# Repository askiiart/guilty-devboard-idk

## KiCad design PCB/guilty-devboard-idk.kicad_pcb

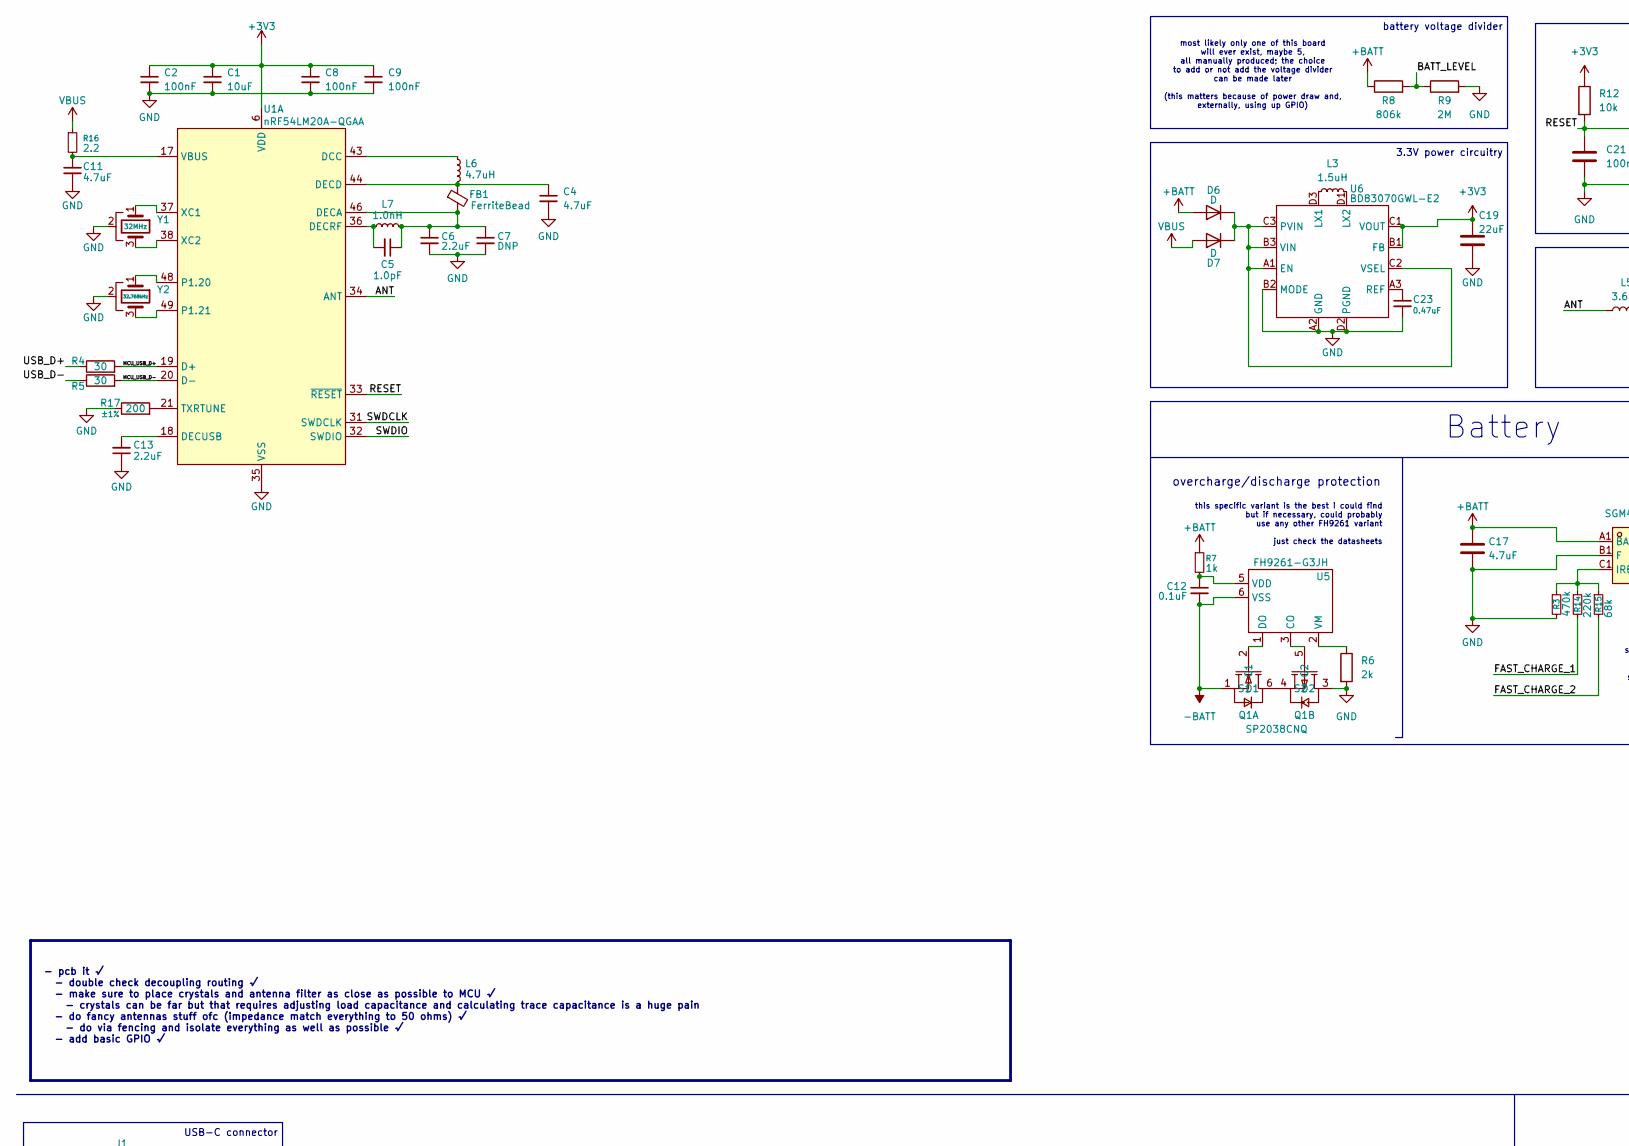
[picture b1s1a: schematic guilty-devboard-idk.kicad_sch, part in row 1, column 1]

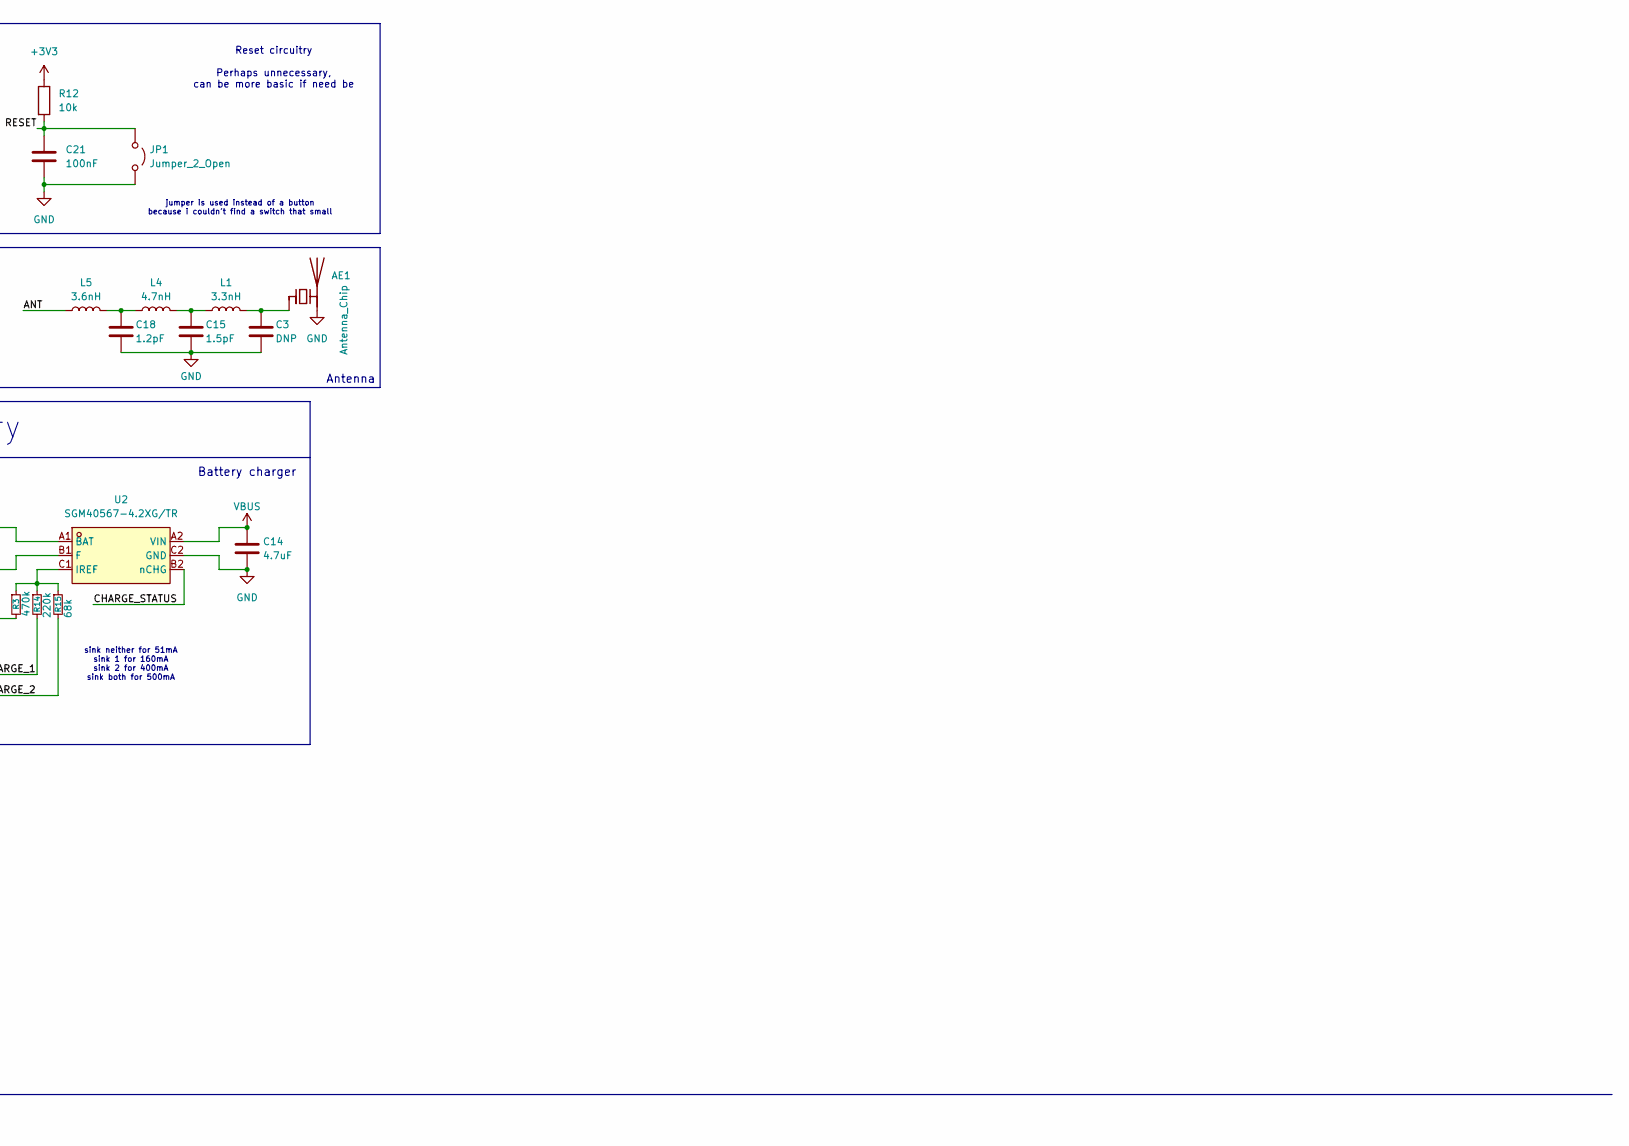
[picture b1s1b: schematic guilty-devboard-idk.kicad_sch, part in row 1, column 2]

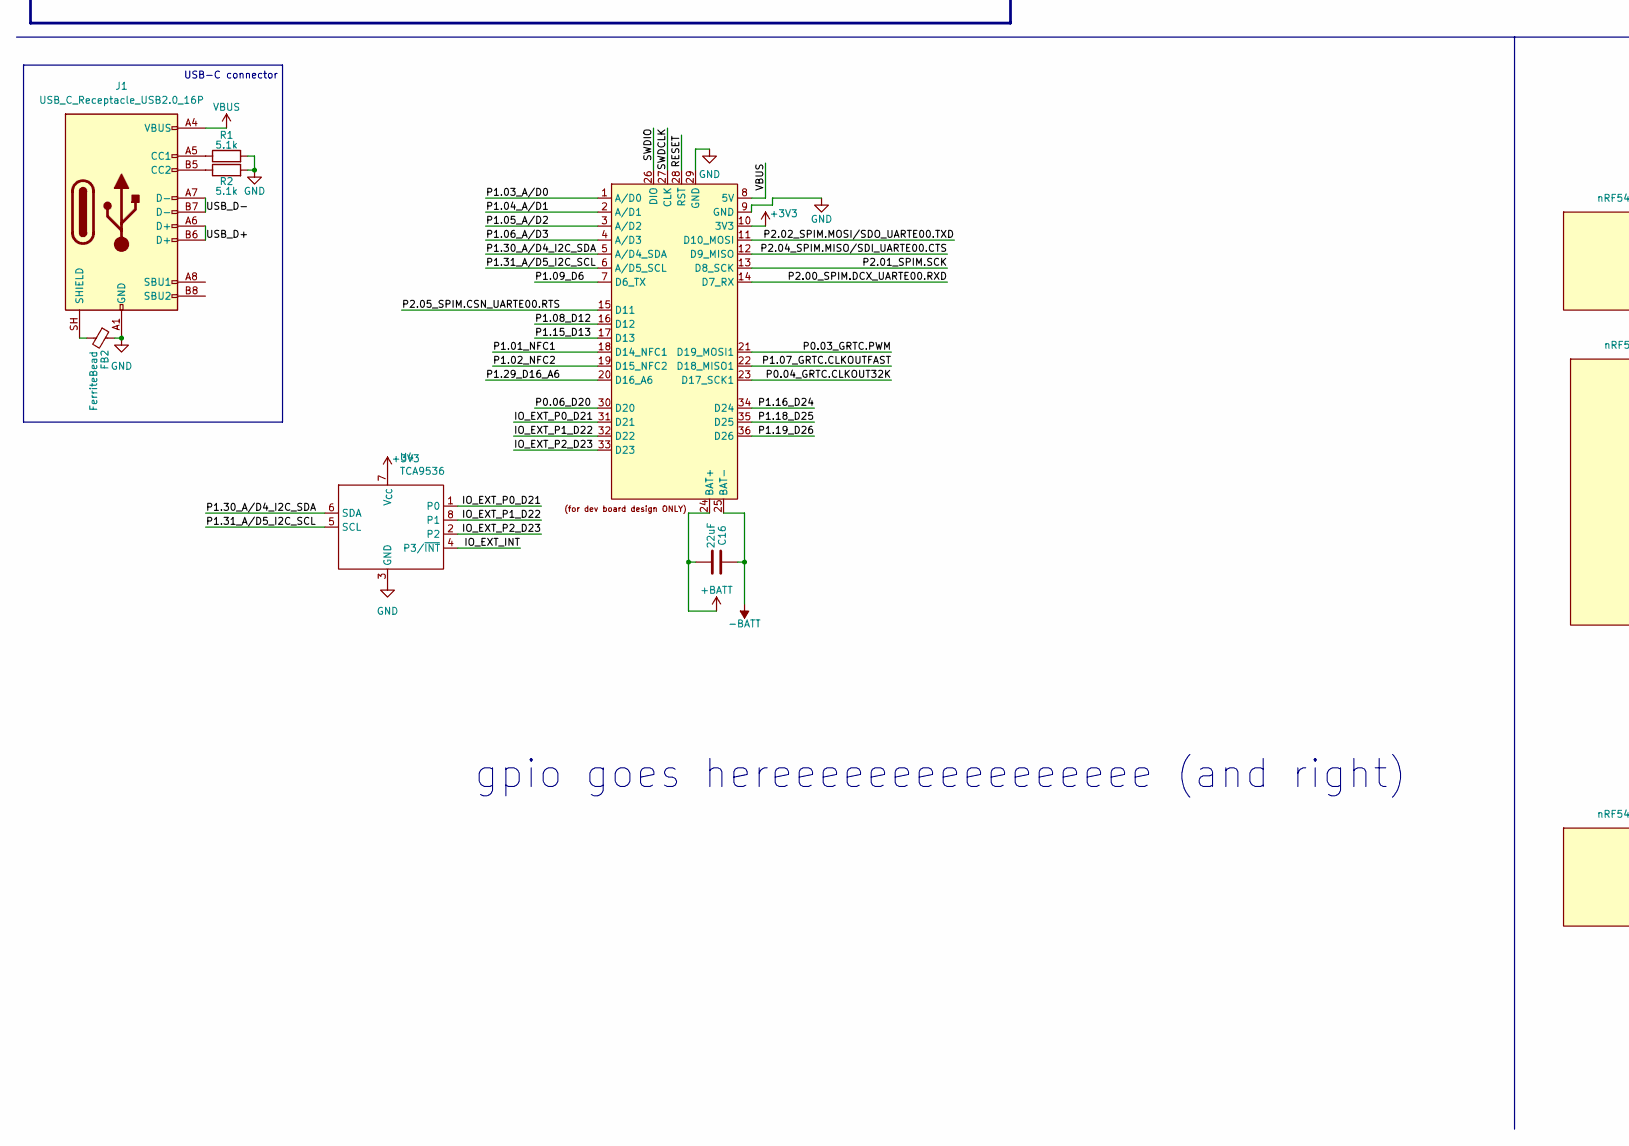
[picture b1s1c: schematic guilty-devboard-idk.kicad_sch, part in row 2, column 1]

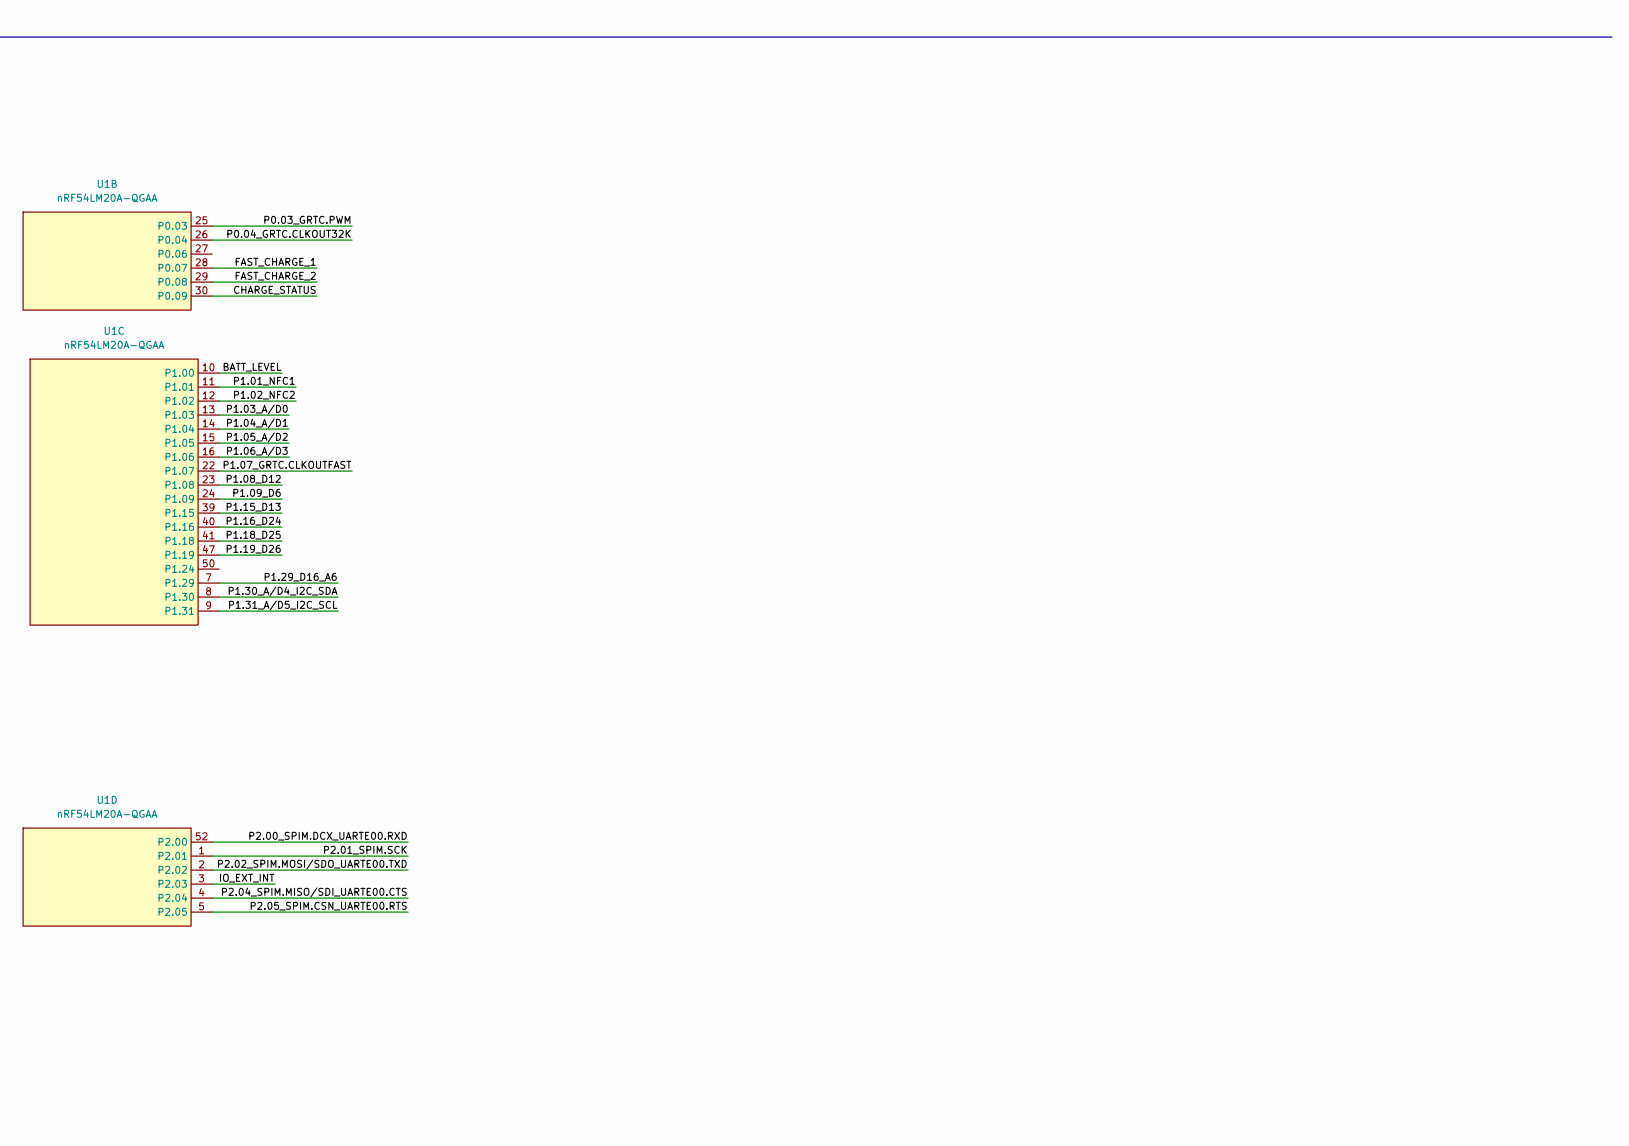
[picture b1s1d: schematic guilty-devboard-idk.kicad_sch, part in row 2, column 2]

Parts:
AE1: Antenna_Chip; 2450AT18D0100001E_L
C1: 10uF; C_0402_1005Metric
C2, C8, C9, C21: 100nF; C_0201_0603Metric
C3, C7: DNP; C_0201_0603Metric
C4, C11, C14, C17: 4.7uF; C_0201_0603Metric
C5: 1.0pF; C_0201_0603Metric
C6, C13: 2.2uF; C_0201_0603Metric
C12: 0.1uF; C_0201_0603Metric
C15: 1.5pF; C_0201_0603Metric
C16, C19: 22uF; C_0402_1005Metric
C18: 1.2pF; C_0201_0603Metric
C23: 0.47uF; C_0201_0603Metric
D6, D7: D; D_SOD-882
FB1, FB2: FerriteBead; L_0201_0603Metric
J1: USB_C_Receptacle_USB2.0_16P; USB_C_Receptacle_Amphenol_124019772112A
JP1: Jumper_2_Open; R_0603_1608Metric
L1: 3.3nH; L_0201_0603Metric
L3: 1.5uH; L_0603_1608Metric
L4: 4.7nH; L_0201_0603Metric
L5: 3.6nH; L_0201_0603Metric
L6: 4.7uH; L_0402_1005Metric
L7: 1.0nH; L_0201_0603Metric
Q1: SP2038CNQ; PDFN-6_L2.0-W2.0-P0.65-BL-EP-1; LCSC Part C41355091
R1, R2: 5.1k; R_0201_0603Metric
R3: 470k; R_0201_0603Metric
R4, R5: 30; R_0201_0603Metric
R6: 2k; R_0201_0603Metric
R7: 1k; R_0201_0603Metric
R8: 806k; R_0201_0603Metric
R9: 2M; R_0201_0603Metric
R12: 10k; R_0201_0603Metric
R14: 220k; R_0201_0603Metric
R15: 68k; R_0201_0603Metric
R16: 2.2; R_0201_0603Metric
R17: 200; R_0201_0603Metric; Tolerance ±1%
U1: nRF54LM20A-QGAA; QFN-52-1EP_6x6mm_P0.4mm_EP4.7x4.7mm_ThermalVias
U2: SGM40567-4.2XG/TR; WLCSP-6_L1.2-W0.9-R3-C2-P0.40-TL; LCSC Part C5141336
U3: Guilty Devboard Xrd pads
U4: TCA9536
U5: FH9261-G3JH; SOT-23-6
U6: BD83070GWL-E2; BD83070GWL
Y1: 32MHz; Crystal_SMD_1210-4Pin_1.2x1.0mm
Y2: 32.768kHz; Crystal_SMD_1210-4Pin_1.2x1.0mm

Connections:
+3V3: C1.1, C2.1, C8.1, C9.1, C19.1, R12.1, U1.6 (VDD), U1.42 (VDD), U1.51 (VDD), U3.10 (3V3), U4.7 (V_{CC}), U6.B1 (FB), U6.C1 (VOUT)
+BATT: C16.2, C17.1, D6.2 (A), R7.1, R8.1, U2.A1 (BAT), U3.24 (BAT+)
-BATT: C12.2, C16.1, Q1.1 (S1), U3.25 (BAT-), U5.6 (VSS)
/ANT: L5.1, U1.34 (ANT)
/BATT_LEVEL: R8.2, R9.1, U1.10 (P1.00)
/CHARGE_STATUS: U1.30 (P0.09), U2.B2 (nCHG)
/FAST_CHARGE_1: R14.2, U1.28 (P0.07)
/FAST_CHARGE_2: R15.2, U1.29 (P0.08)
/IO_EXT_INT: U1.3 (P2.03), U4.4 (P3/~INT)
/IO_EXT_P0_D21: U3.31 (D21), U4.1 (P0)
/IO_EXT_P1_D22: U3.32 (D22), U4.8 (P1)
/IO_EXT_P2_D23: U3.33 (D23), U4.2
/MCU_USB_D+: R4.2, U1.19 (D+)
/MCU_USB_D-: R5.2, U1.20 (D-)
/P0.03_GRTC.PWM: U1.25 (P0.03), U3.21 (D19_MOSI1)
/P0.04_GRTC.CLKOUT32K: U1.26 (P0.04), U3.23 (D17_SCK1)
/P0.06_D20: U3.30 (D20)
/P1.01_NFC1: U1.11 (P1.01), U3.18 (D14_NFC1)
/P1.02_NFC2: U1.12 (P1.02), U3.19 (D15_NFC2)
/P1.03_A/D0: U1.13 (P1.03), U3.1 (A/D0)
/P1.04_A/D1: U1.14 (P1.04), U3.2 (A/D1)
/P1.05_A/D2: U1.15 (P1.05), U3.3 (A/D2)
/P1.06_A/D3: U1.16 (P1.06), U3.4 (A/D3)
/P1.07_GRTC.CLKOUTFAST: U1.22 (P1.07), U3.22 (D18_MISO1)
/P1.08_D12: U1.23 (P1.08), U3.16 (D12)
/P1.09_D6: U1.24 (P1.09), U3.7 (D6_TX)
/P1.15_D13: U1.39 (P1.15), U3.17 (D13)
/P1.16_D24: U1.40 (P1.16), U3.34 (D24)
/P1.18_D25: U1.41 (P1.18), U3.35 (D25)
/P1.19_D26: U1.47 (P1.19), U3.36 (D26)
/P1.29_D16_A6: U1.7 (P1.29), U3.20 (D16_A6)
/P1.30_A/D4_I2C_SDA: U1.8 (P1.30), U3.5 (A/D4_SDA), U4.6 (SDA)
/P1.31_A/D5_I2C_SCL: U1.9 (P1.31), U3.6 (A/D5_SCL), U4.5 (SCL)
/P2.00_SPIM.DCX_UARTE00.RXD: U1.52 (P2.00), U3.14 (D7_RX)
/P2.01_SPIM.SCK: U1.1 (P2.01), U3.13 (D8_SCK)
/P2.02_SPIM.MOSI/SDO_UARTE00.TXD: U1.2 (P2.02), U3.11 (D10_MOSI)
/P2.04_SPIM.MISO/SDI_UARTE00.CTS: U1.4 (P2.04), U3.12 (D9_MISO)
/P2.05_SPIM.CSN_UARTE00.RTS: U1.5 (P2.05), U3.15 (D11)
/RESET: C21.1, JP1.1 (A), R12.2, U1.33 (~RESET), U3.28 (RST)
/SWDCLK: U1.31 (SWDCLK), U3.27 (CLK)
/SWDIO: U1.32 (SWDIO), U3.26 (DIO)
/USB_D+: J1.A6 (D+), J1.B6 (D+), R4.1
/USB_D-: J1.A7 (D-), J1.B7 (D-), R5.1
GND: AE1.2 (PCB_Trace), C1.2, C2.2, C3.1, C4.2, C6.2, C7.2, C8.2, C9.2, C11.2, C13.1, C14.2, C15.1, C17.2, C18.1, C19.2, C21.2, C23.2, FB2.1, J1.A1 (GND), J1.A12 (GND), J1.B1 (GND), J1.B12 (GND), JP1.2 (B), Q1.3 (D2), R1.2, R2.2, R3.2, R6.2, R9.2, R17.1, U1.35 (VSS), U1.45 (VSS), U1.53 (VSS), U2.B1 (F), U2.C2 (GND), U3.9 (GND), U3.29 (GND), U4.3 (GND), U6.A2 (GND), U6.B2 (MODE), U6.D2 (PGND), Y1.2, Y2.2
unnamed: AE1.1 (FEED), C3.2, L1.2
unnamed: C15.2, L1.1, L4.2
unnamed: C18.2, L4.1, L5.2
unnamed: D6.1 (K), D7.1 (K), U6.A1 (EN), U6.B3 (VIN), U6.C2 (VSEL), U6.C3 (PVIN)
unnamed: J1.A5 (CC1), R1.1
unnamed: J1.B5 (CC2), R2.1
unnamed: FB2.2, J1.SH (SHIELD)
unnamed: Q1.4 (S2), Q1.6 (D1)
unnamed: Q1.2 (G1), U5.1 (DO)
unnamed: Q1.5 (G2), U5.3 (CO)
unnamed: L6.1, U1.43 (DCC)
unnamed: C5.1, C6.1, C7.1, FB1.2, L7.2, U1.46 (DECA)
unnamed: C4.1, FB1.1, L6.2, U1.44 (DECD)
unnamed: C5.2, L7.1, U1.36 (DECRF)
unnamed: C13.2, U1.18 (DECUSB)
unnamed: U1.48 (P1.20), Y2.1
unnamed: U1.49 (P1.21), Y2.3
unnamed: R17.2, U1.21 (TXRTUNE)
unnamed: C11.1, R16.2, U1.17 (VBUS)
unnamed: U1.37 (XC1), Y1.1
unnamed: U1.38 (XC2), Y1.3
unnamed: R3.1, R14.1, R15.1, U2.C1 (IREF)
unnamed: C12.1, R7.2, U5.5 (VDD)
unnamed: R6.1, U5.2 (VM)
unnamed: L3.1, U6.D3 (LX1)
unnamed: L3.2, U6.D1 (LX2)
unnamed: C23.1, U6.A3 (REF)
VBUS: C14.1, D7.2 (A), J1.A4 (VBUS), J1.A9 (VBUS), J1.B4 (VBUS), J1.B9 (VBUS), R16.1, U2.A2 (VIN), U3.8 (5V)

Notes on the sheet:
Reset circuitry Perhaps unnecessary, can be more basic if need be
Battery charger
battery voltage divider
- pcb it √ - double check decoupling routing √ - make sure to place crystals and antenna filter as close as possible to MCU √ - crystals can be far but that requires adjusting load capacitance and calculating trace capacitance is a huge pain - do fancy antennas stuff ofc (impedance match everything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
jumper is used instead of a button because i couldn't find a switch that small
this specific variant is the best i could find but if necessary, could probably use any other FH9261 variant just check the datasheets
Antenna
USB-C connector
gpio goes hereeeeeeeeeeeeeeee (and right)
Battery
overcharge/discharge protection
3.3V power circuitry
sink neither for 51mA sink 1 for 160mA sink 2 for 400mA sink both for 500mA
most likely only one of this board will ever exist, maybe 5, all manually produced; the choice to add or not add the voltage divider can be made later (this matters because of power draw and, externally, using up GPIO)

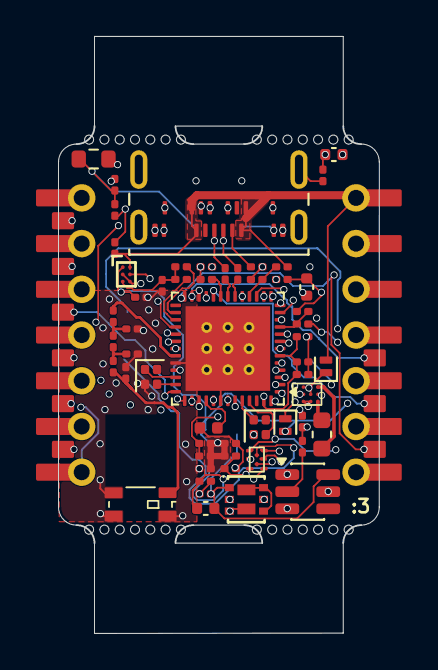
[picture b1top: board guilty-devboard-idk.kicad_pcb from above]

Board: 6 copper layers, 17.8 x 33.2 mm, 56 parts (0 on the bottom side), 71 nets.

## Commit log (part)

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2026-01-15 initial version - pretty much finished schematic
2026-01-16 fixed power and added switch RF (dual antennas)
2026-01-21 add libs for p+n channel mosfet and battery pads
2026-01-26 add some comments, component selection, and switch to different boost converter
